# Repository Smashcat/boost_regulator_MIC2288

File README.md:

# boost_regulator_MIC2288

Small boost regulator board designed for use on breadboards. Will supply a 12V, 150mA output from a 3v-9v input.

Please note that the "VOUT" LED should be omitted to achieve the maximum output current. If you only require around 100mA or less, it can be populated to indicate the output state.

3D model render with CAD download can be found [here](https://a360.co/3hNGanB)

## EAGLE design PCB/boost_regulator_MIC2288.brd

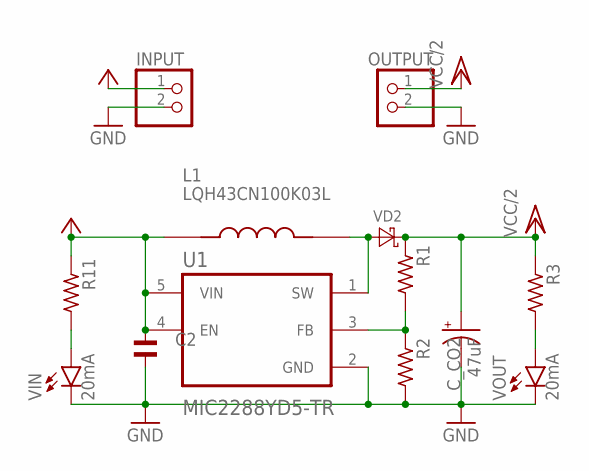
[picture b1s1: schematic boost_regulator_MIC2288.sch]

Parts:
C2: 10uF; RC-MASTER-SMD_C0603MP
C_CO2: 47uF; PANASONIC_C
INPUT: PINHD-1X2; 1X02
L1: LQH43CN100K03L; IND_LQH43CN100K03L
OUTPUT: PINHD-1X2; 1X02
R1: 47K; RC-MASTER-SMD_R0603MP
R2: 5K1; RC-MASTER-SMD_R0603MP
R3: 1K; RC-MASTER-SMD_R0603MP
R11: 100R; RC-MASTER-SMD_R0603MP
U1: MIC2288YD5-TR; SOT95P280X100-5N
VD2: DIODE-SCHOTTKY-SOD123; SOD123
VIN: 20mA; CHIP-LED0603
VOUT: 20mA; CHIP-LED0603

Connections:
ACTIVITY: R11.2, VIN.A
ACTIVITY1: R3.2, VOUT.A
GND: C2.2, C_CO2.-, INPUT.2, OUTPUT.2, R2.2, U1.2 (GND), VIN.C, VOUT.C
unnamed: L1.2, U1.1 (SW), VD2.A
unnamed: R1.2, R2.1, U1.3 (FB)
VCC: C2.1, INPUT.1, L1.1, R11.1, U1.4 (EN), U1.5 (VIN)
VCC/2: C_CO2.+, OUTPUT.1, R1.1, R3.1, VD2.C

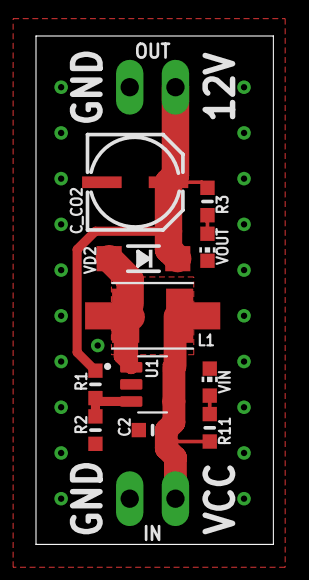
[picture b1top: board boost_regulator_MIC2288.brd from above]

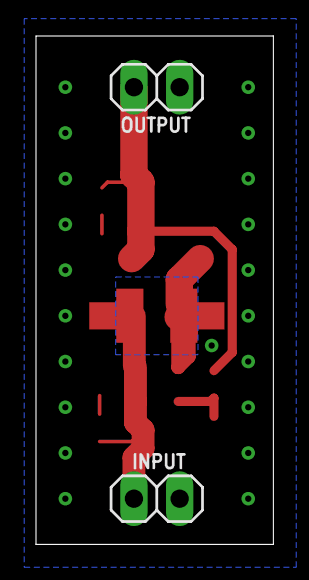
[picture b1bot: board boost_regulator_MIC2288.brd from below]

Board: 2 copper layers, 13.2 x 28.2 mm, 13 parts (2 on the bottom side), 7 nets.

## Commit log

2020-09-20 Added files
2020-09-30 Changed resistor values, edited description
2020-09-30 Changed track widths slightly

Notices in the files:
parts and their libraries:
SparkFun-Capacitors: Licensing: Creative Commons ShareAlike 4.0 International - https://creativecommons.org/licenses/by-sa/4.0
